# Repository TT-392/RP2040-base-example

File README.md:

# RP2040-base-example
A simple dev board, created to test [RP2040-base](https://github.com/TT-392/RP2040-base)

Revision 0.9 was produced at jlcpcb. The rev number was bumped to 1.0 after the pcb was tested. There were no changes between rev 0.9 and 1.0. The production files in the "jlcpcb" folder are identical to the ones used to order the pcbs.

There seems to be one serious bug in the design, see "known issues" nr 1

revision 0.9 of the pcb

# Tested functionality physical board rev 0.9 (identical to 1.0)
A sketch has been uploaded, which prints a string over cdc usb every second. This indicates working usb functionality, and working program memory.

After unplugging and plugging the board back in, the board doesn't seem to correctly start, see known issue nr 1.

# Notes
- jlcpcb has no basic part 27 ohm resistors, therefore, when ordering the test pcbs, the series termination resistors on the usb lines were replaced with 22 ohm ones (not too critical but not ideal)

# Known issues
1. There is something wrong with the chrystal setup, experiences the same issues as the adafruid boards mentioned in: https://github.com/raspberrypi/pico-sdk/pull/457. This can be fixed by setting PICO_XOSC_STARTUP_DELAY_MULTIPLIER to 64, like mentioned there.
2. No thought was given to which IO pins should be exposed, no analog pins have been exposed.
3. No debug LED.
4. ground plane on top layer wasn't taken into account when calculating trace with for usb line impedance matching (not too critical but not ideal)

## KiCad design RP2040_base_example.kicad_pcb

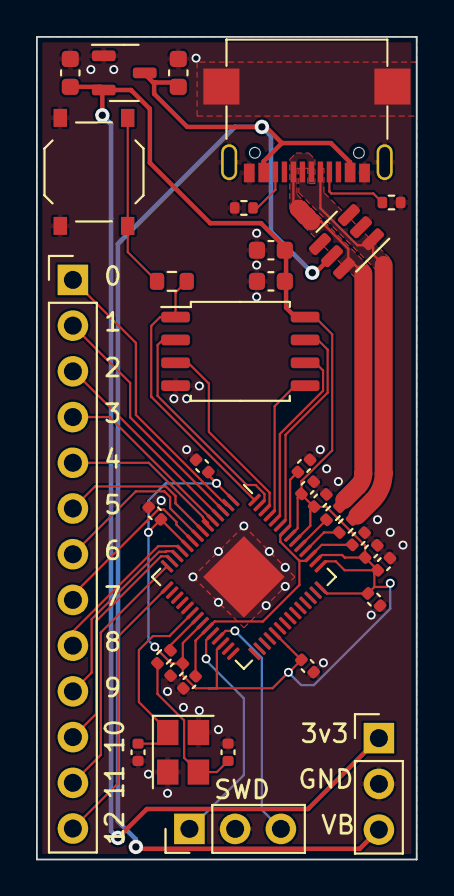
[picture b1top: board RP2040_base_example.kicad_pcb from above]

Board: 2 copper layers, 21.1 x 45.7 mm, 34 parts (0 on the bottom side), 35 nets.

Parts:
C1, C2: 1u; C_0603_1608Metric
C3, C4, C5, C6, C7, C8, C9, C10, C11, C12: 100n; C_0402_1005Metric
C13, C14: 1u; C_0402_1005Metric
C15, C16: 30p; C_0402_1005Metric
C17: 100n; C_0603_1608Metric
C18: 10n; C_0603_1608Metric
J1: Conn_01x03; PinHeader_1x03_P2.54mm_Vertical
J2: Conn_01x13; PinHeader_1x13_P2.54mm_Vertical
J3: GT-USB-7047C
R1, R2: 5k1; R_0402_1005Metric
R3, R4: 27; R_0402_1005Metric
R5: 1k; R_0402_1005Metric
R6: 1k; R_0603_1608Metric
SW1: SW_Push; TS-1187A
SWD1: Conn_01x03; PinHeader_1x03_P2.54mm_Vertical
U1: XC6206P332MR; SOT-23-3_flipped_for_jlcpcb
U2: SRV05-4; SOT-23-6_flipped_for_jlcpcb
U3: RP2040; QFN-56-1EP_7x7mm_P0.4mm_EP3.2x3.2mm
U4: W25QXXXJV; SOIC-8_5.275x5.275mm_P1.27mm
Y1: X322512MSB4SI; YSX321SL, datasheet recommended measurements

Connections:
+3V3: C2.1, C5.1, C6.1, C7.1, C8.1, C9.1, C10.1, C11.1, C12.1, C14.1, C17.1, C18.1, J1.1, U1.2 (VO), U3.1 (IOVDD), U3.10 (IOVDD), U3.22 (IOVDD), U3.26 (RUN), U3.33 (IOVDD), U3.42 (IOVDD), U3.43 (ADC_AVDD), U3.44 (VREG_IN), U3.48 (USB_VDD), U3.49 (IOVDD), U4.8 (VCC)
/RP2040-base/1V1: C3.1, C4.1, C13.1, U3.23 (DVDD), U3.45 (VREG_VOUT), U3.50 (DVDD)
/RP2040-base/GPIO0: J2.1, U3.2 (GPIO0)
/RP2040-base/GPIO1: J2.2, U3.3 (GPIO1)
/RP2040-base/GPIO2: J2.3, U3.4 (GPIO2)
/RP2040-base/GPIO3: J2.4, U3.5 (GPIO3)
/RP2040-base/GPIO4: J2.5, U3.6 (GPIO4)
/RP2040-base/GPIO5: J2.6, U3.7 (GPIO5)
/RP2040-base/GPIO6: J2.7, U3.8 (GPIO6)
/RP2040-base/GPIO7: J2.8, U3.9 (GPIO7)
/RP2040-base/GPIO8: J2.9, U3.11 (GPIO8)
/RP2040-base/GPIO9: J2.10, U3.12 (GPIO9)
/RP2040-base/GPIO10: J2.11, U3.13 (GPIO10)
/RP2040-base/GPIO11: J2.12, U3.14 (GPIO11)
/RP2040-base/GPIO12: J2.13, U3.15 (GPIO12)
/RP2040-base/QSPI_SCLK: U3.52 (QSPI_SCLK), U4.6 (CLK)
/RP2040-base/QSPI_SD0: U3.53 (QSPI_SD0), U4.5 (DI(IO0))
/RP2040-base/QSPI_SD1: U3.55 (QSPI_SD1), U4.2 (DO(IO1))
/RP2040-base/QSPI_SD2: U3.54 (QSPI_SD2), U4.3 (IO2)
/RP2040-base/QSPI_SD3: U3.51 (QSPI_SD3), U4.7 (IO3)
/RP2040-base/QSPI_SS: R6.1, U3.56 (QSPI_SS), U4.1 (~CS)
/RP2040-base/SWCLK: SWD1.1, U3.24 (SWCLK)
/RP2040-base/SWD: SWD1.3, U3.25 (SWD)
/RP2040-base/USB_D+: J3.A6 (D+), J3.B6 (D+), R3.1, U2.6 (IO4)
/RP2040-base/USB_D-: J3.A7 (D-), J3.B7 (D-), R4.1, U2.1 (IO1)
/RP2040-base/XIN: C15.1, U3.20 (XIN), Y1.1
/RP2040-base/XOUT: R5.1, U3.21 (XOUT)
/RP2040-base/~USB_BOOT: R6.2, SW1.2
GND: C1.2, C2.2, C3.2, C4.2, C5.2, C6.2, C7.2, C8.2, C9.2, C10.2, C11.2, C12.2, C13.2, C14.2, C15.2, C16.2, C17.2, C18.2, J1.2, J3.A1 (GND), J3.A12 (GND), J3.B1 (GND), J3.B12 (GND), J3.S1 (SHIELD), R1.2, R2.2, SW1.1, SWD1.2, U1.1 (GND), U2.2 (VN), U2.3 (IO2), U2.4 (IO3), U3.19 (TESTEN), U3.57 (GND), U4.4 (GND), Y1.2, Y1.4
unnamed: C16.1, R5.2, Y1.3
unnamed: J3.A5 (CC1), R1.1
unnamed: J3.B5 (CC2), R2.1
unnamed: R4.2, U3.46 (USB_DM)
unnamed: R3.2, U3.47 (USB_DP)
VBUS: C1.1, J1.3, J3.A4 (VBUS), J3.A9 (VBUS), J3.B4 (VBUS), J3.B9 (VBUS), U1.3 (VI), U2.5 (VP)

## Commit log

2023-08-01 Improve ground path around voltage regulator
2023-08-21 Add readme
2023-08-21 Bump version number
2023-08-21 Improve documentation and spelling
2024-01-04 Mention startup issues in readme
